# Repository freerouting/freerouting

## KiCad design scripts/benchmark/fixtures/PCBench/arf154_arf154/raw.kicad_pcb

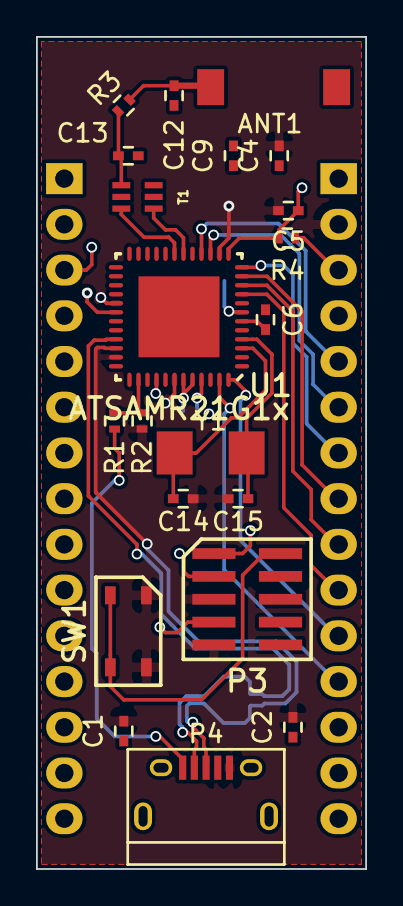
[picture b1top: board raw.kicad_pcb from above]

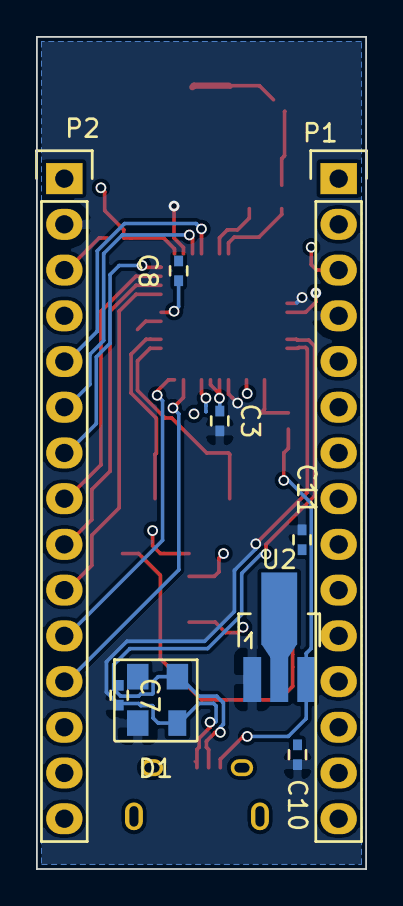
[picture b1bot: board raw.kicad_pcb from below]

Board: 4 copper layers, 18.3 x 46.2 mm, 30 parts (9 on the bottom side), 26 nets.

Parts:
ANT1: antenna; CHIPANTENNA2dBi
C1: 10uF; C_0402
C2, C3, C4, C5, C6, C7, C8, C10: 100n; C_0402
C9, C11: 10u; C_0402
C12, C13: xF; C_0402
C14, C15: 18pF; C_0402
D1: PRTR5V0U2X; SOT143B
P1: Cn1; Pin_Header_Straight_1x15
P2: Cn2; Pin_Header_Straight_1x15
P3: CONN_02X05; CMxDBG
P4: USB_B; USB_Micro-B
R1, R2: 100K; R_0402
R3: xR; R_0402
R4: 10K; R_0402
SW1: SW_PUSH; tactileswitch
T1: 2450BM15A0015; JBALUN
U1: ATSAMR21G1x; QFN48EP
U2: AZ1117C; SOT89-3_Housing_Handsoldering
Y1: 16MHz; 2SMD

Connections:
/MainProcessor/BD+: T1.4, U1.18
/MainProcessor/BD-: T1.3, U1.19
/MainProcessor/PA4: P2.10, U1.9
/MainProcessor/PA5: P2.9, U1.10
/MainProcessor/PA6: P2.8, U1.11
/MainProcessor/PA7: P2.7, U1.12
/MainProcessor/PA8: P2.6, U1.15
/MainProcessor/PA9: P2.5, U1.16
/MainProcessor/PA23: R1.2, R2.1, U1.32
/MainProcessor/PB2: P2.12, U1.47
/MainProcessor/PB3: P2.11, U1.48
/MainProcessor/RST: C7.1, P1.3, P2.3, P3.10, R4.1, SW1.2, U1.40
/MainProcessor/SWCLK: P3.4, U1.45
/MainProcessor/SWDIO: P3.2, U1.46
/Sheet557215E3/D+: D1.3, P4.2, U1.33
/Sheet557215E3/D-: D1.2, P4.3, U1.34
GND: C1.2, C2.2, C3.2, C4.2, C5.2, C7.2, C10.2, C11.2, C14.2, C15.2, D1.1, P1.4, P2.2, P3.3, P3.5, P3.9, P4.4, P4.5, R2.2, SW1.1, U1.14, U1.29, U1.35, U1.42, U2.1
GNDA: C6.2, C8.2, C9.2, U1.5, U1.8, U1.17, U1.20
GNDREF: C12.2, C13.2, T1.2, T1.5, T1.6
unnamed: ANT1.1, C12.1, R3.2
unnamed: C13.1, R3.1, T1.1
unnamed: C14.1, U1.3, Y1.1
unnamed: C15.1, U1.4, Y1.2
VAA: C6.1, C8.1, C9.1, U1.6, U1.7
VCC: C10.1, D1.4, P4.1, R1.1, U2.3
VDD: C1.1, C2.1, C3.1, C4.1, C5.1, C11.1, P2.14, P3.1, R4.2, U1.13, U1.30, U1.36, U1.43, U1.44, U2.2

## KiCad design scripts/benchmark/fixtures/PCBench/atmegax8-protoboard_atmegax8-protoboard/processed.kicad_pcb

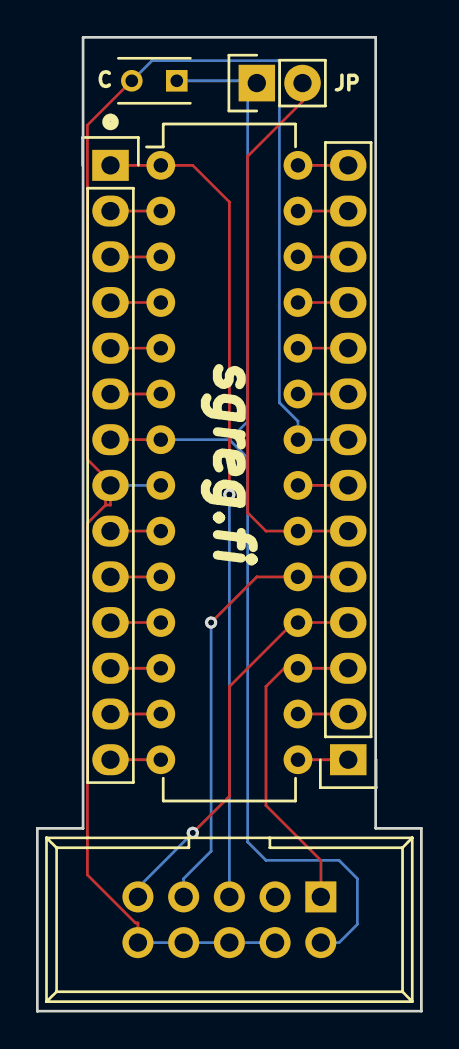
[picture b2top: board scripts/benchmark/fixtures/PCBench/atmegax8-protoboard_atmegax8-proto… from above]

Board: 2 copper layers, 21.3 x 54.1 mm, 6 parts (0 on the bottom side), 27 nets.

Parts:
C1: 100n; C_Rect_L4_W2.5_P2.5
IC1: ATMEGA328-P; DIP-28_W7.62mm
JP1: JUMPER; Socket_Strip_Straight_1x02
P1: CONN1; Socket_Strip_Straight_1x14
P2: CONN2; Socket_Strip_Straight_1x14
P3: SERPROG; IDC_Header_Straight_10pins

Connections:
/AREF: IC1.21, P2.7
/AVCC: IC1.20, JP1.2, P2.6
/GND: C1.2, IC1.8, IC1.22, P1.8, P2.8, P3.4, P3.6, P3.8, P3.10
/PB0: IC1.14, P1.14
/PB1: IC1.15, P2.1
/PB2: IC1.16, P2.2
/PB3: IC1.17, P2.3, P3.1
/PB4: IC1.18, P2.4, P3.9
/PB5: IC1.19, P2.5, P3.7
/PB6: IC1.9, P1.9
/PB7: IC1.10, P1.10
/PC0: IC1.23, P2.9
/PC1: IC1.24, P2.10
/PC2: IC1.25, P2.11
/PC3: IC1.26, P2.12
/PC4: IC1.27, P2.13
/PC5: IC1.28, P2.14
/PD0: IC1.2, P1.2
/PD1: IC1.3, P1.3
/PD2: IC1.4, P1.4
/PD3: IC1.5, P1.5
/PD4: IC1.6, P1.6
/PD5: IC1.11, P1.11
/PD6: IC1.12, P1.12
/PD7: IC1.13, P1.13
/RESET: IC1.1, P1.1, P3.5
/VCC: C1.1, IC1.7, JP1.1, P1.7, P3.2

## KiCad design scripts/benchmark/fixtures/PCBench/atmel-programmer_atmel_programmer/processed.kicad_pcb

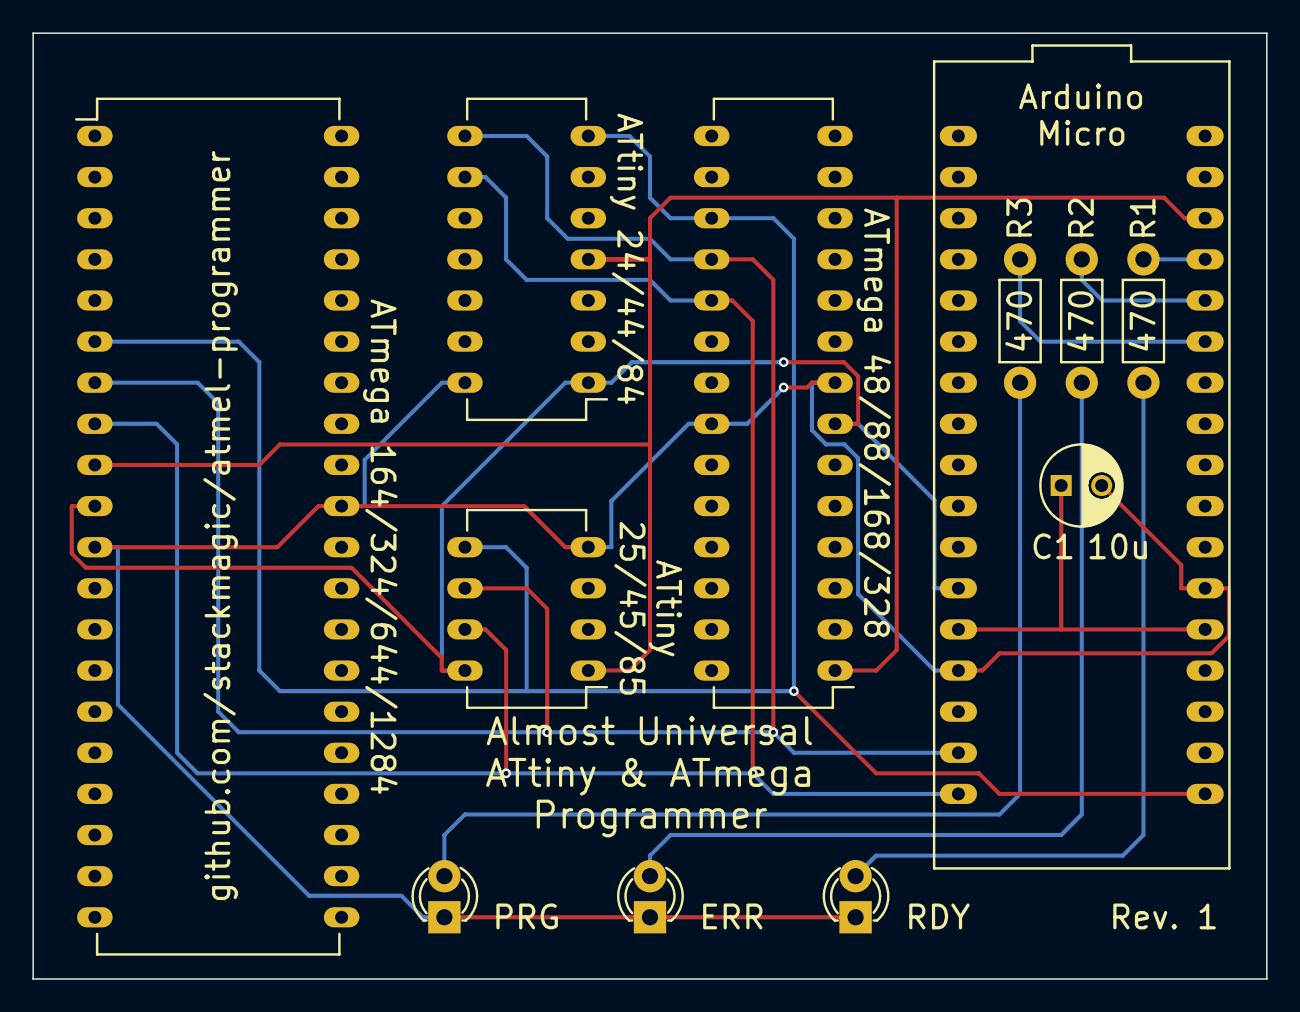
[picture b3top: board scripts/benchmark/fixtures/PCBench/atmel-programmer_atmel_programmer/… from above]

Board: 2 copper layers, 76.2 x 58.4 mm, 12 parts (0 on the bottom side), 13 nets.

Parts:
C1: 10u; C_Radial_D5_L6_P2.5
D1, D2, D3: LED; LED-3MM
IC1: ATTINY85-P; DIP-8_W7.62mm_LongPads
IC2: ATTINY84-P; DIP-14_W7.62mm_LongPads
IC3: ATMEGA328-P; DIP-28_W7.62mm_LongPads
IC4: ATMEGA1284-P; DIP-40_W15.24mm_LongPads
R1, R2, R3: 470; Resistor_Horizontal_RM7mm
U1: Arduino_Micro_ISP; ArduinoMicro

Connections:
GND: C1.2, D1.1, D2.1, D3.1, IC1.4, IC2.14, IC3.8, IC3.22, IC4.11, IC4.31, U1.14, U1.23
MISO: IC1.6, IC2.8, IC3.18, IC4.7, U1.16
MOSI: IC1.5, IC2.7, IC3.17, IC4.6, U1.18
unnamed: C1.1, U1.13, U1.22
unnamed: D1.2, R1.1
unnamed: D2.2, R2.1
unnamed: D3.2, R3.1
unnamed: R1.2, U1.31
unnamed: R2.2, U1.30
unnamed: R3.2, U1.29
RST: IC1.1, IC2.4, IC3.1, IC4.9, U1.32
SCK: IC1.7, IC2.9, IC3.19, IC4.8, U1.17
VCC: IC1.8, IC2.1, IC3.7, IC4.10, U1.12

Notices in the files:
scripts/benchmark/fixtures/PCBench/atmegax8-protoboard_atmegax8-protoboard/processed.kicad_pcb:
Licensed under CERN OHDL v.1.2
